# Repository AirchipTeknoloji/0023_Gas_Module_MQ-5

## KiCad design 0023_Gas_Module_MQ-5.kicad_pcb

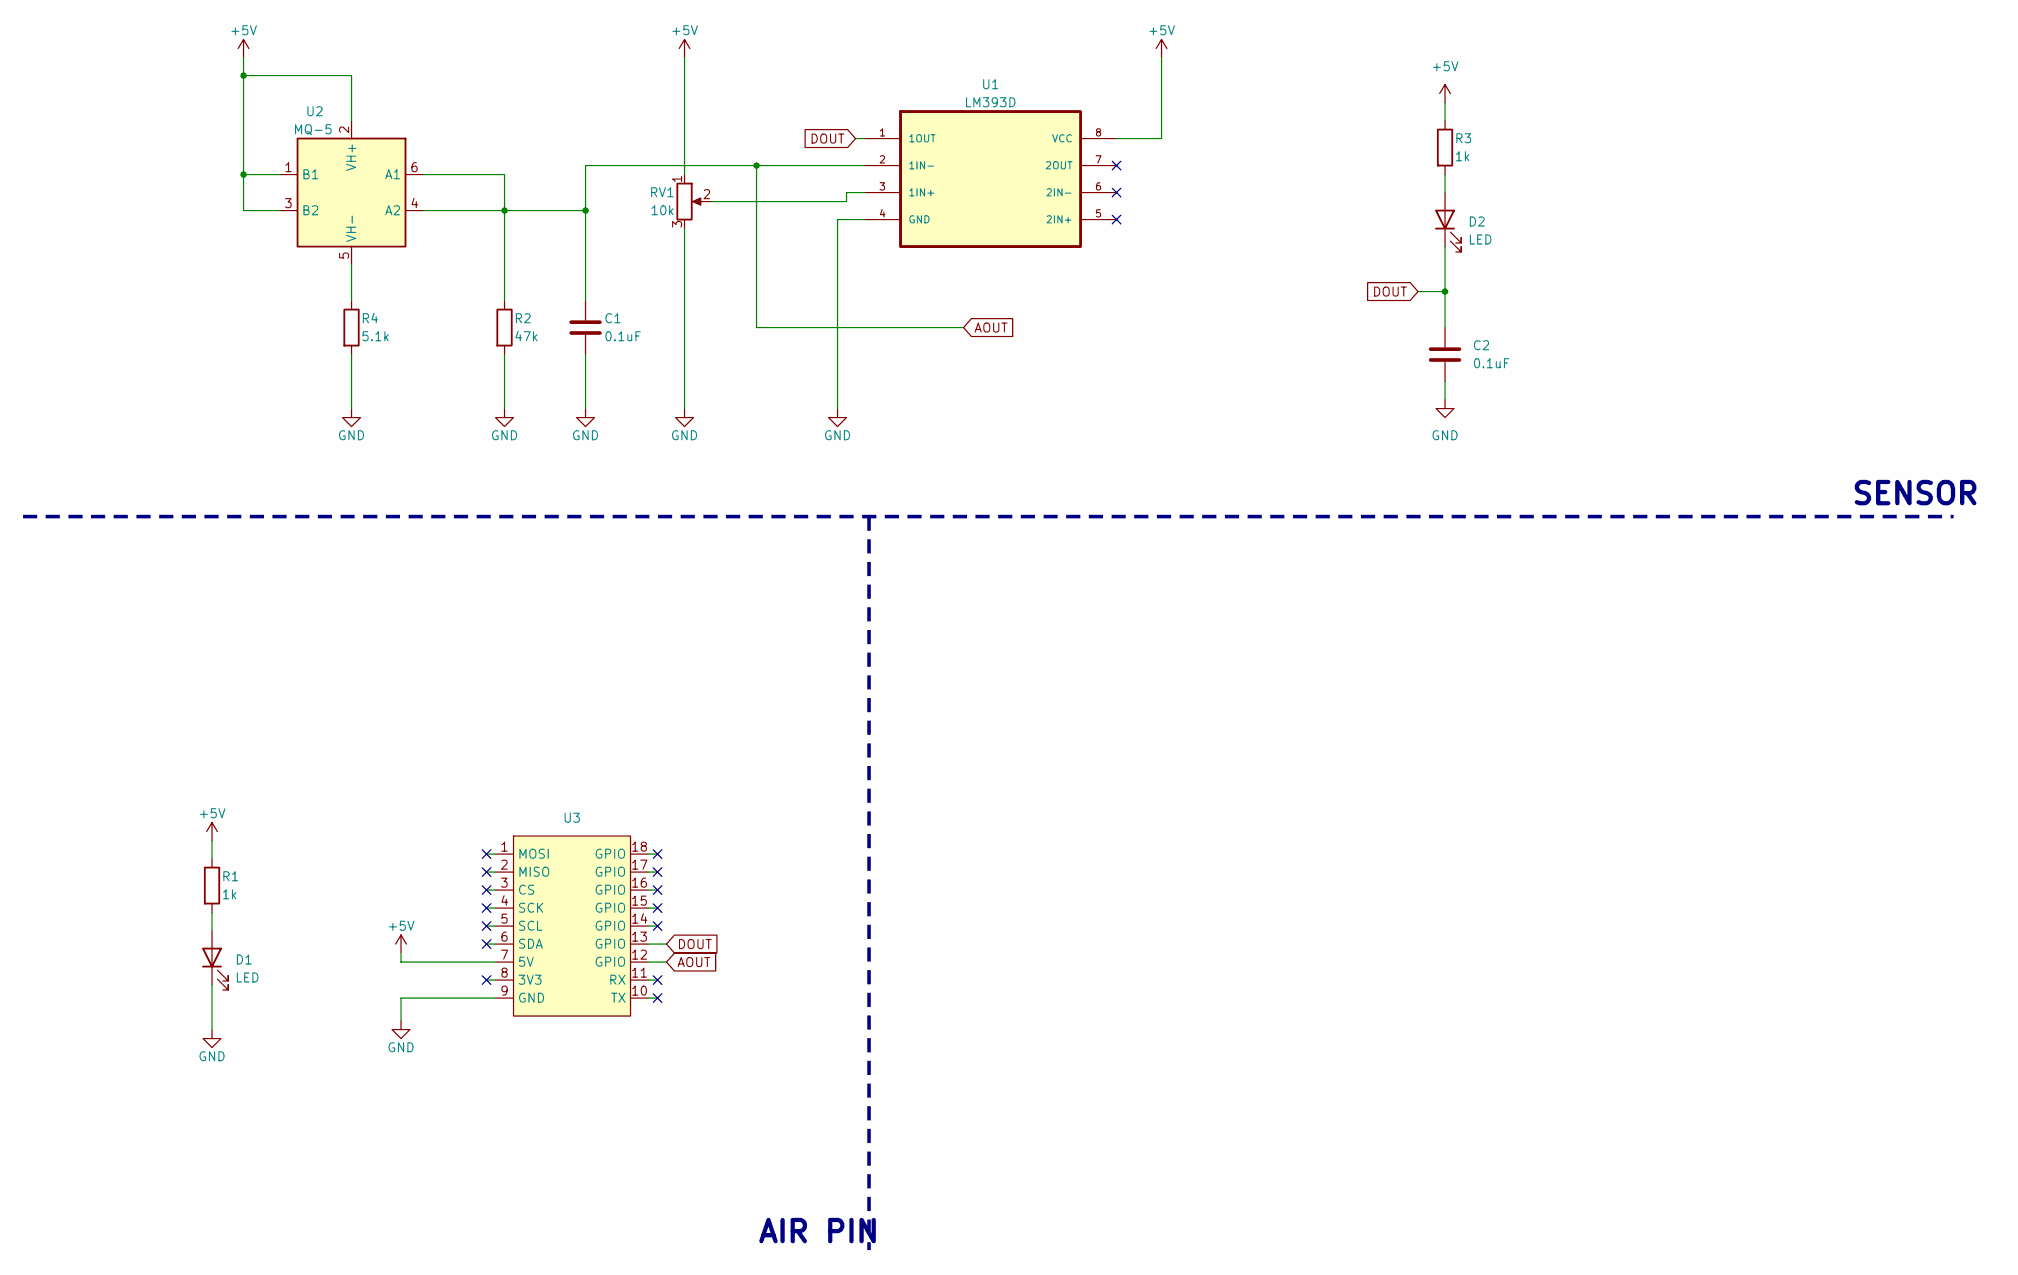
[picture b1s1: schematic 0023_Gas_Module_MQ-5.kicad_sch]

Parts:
C1, C2: 0.1uF; C_0805_2012Metric
D1, D2: LED; LED_0805_2012Metric
R1, R3: 1k; R_0805_2012Metric
R2: 47k; R_0805_2012Metric
R4: 5.1k; R_0805_2012Metric
RV1: 10k; 3362P_1
U1: LM393D; SOIC127P599X175-8N
U2: MQ-5; MQ-6
U3: air_module

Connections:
+5V: R1.1, R3.1, RV1.1, U1.8 (VCC), U2.1 (B1), U2.2 (VH+), U2.3 (B2), U3.7 (5V); also elsewhere on the board
AOUT: C1.1, R2.1, U1.2 (1IN-), U2.4 (A2), U2.6 (A1), U3.12 (GPIO)
DOUT: C2.1, D2.1 (K), U1.1 (1OUT), U3.13 (GPIO)
GND: C1.2, C2.2, D1.1 (K), R2.2, R4.2, RV1.3, U1.4 (GND), U3.9 (GND); also elsewhere on the board
unnamed: D1.2 (A), R1.2
unnamed: D2.2 (A), R3.2
unnamed 6: RV1.2, U1.3 (1IN+); also elsewhere on the board
unnamed: R4.1, U2.5 (VH-)

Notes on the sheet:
SENSOR
AIR PIN

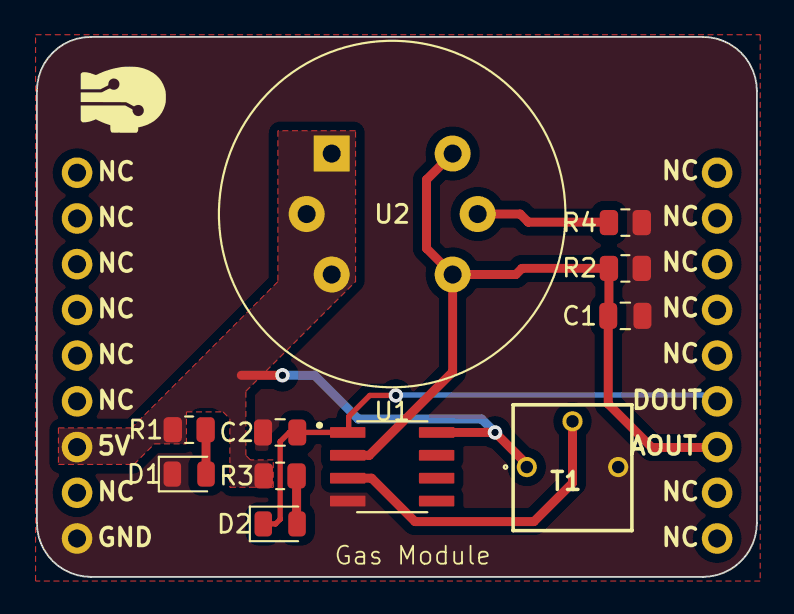
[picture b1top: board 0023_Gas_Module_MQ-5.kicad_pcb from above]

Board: 2 copper layers, 40.0 x 30.0 mm, 12 parts (0 on the bottom side), 8 nets.

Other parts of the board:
T1: 10k; 3362P_1

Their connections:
+5V: T1.1; also elsewhere on the board
GND: T1.3; also elsewhere on the board
unnamed 6: T1.2; also elsewhere on the board
